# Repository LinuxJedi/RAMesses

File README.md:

# RAMesses

RAMesses is a plug and play Amiga 500/2000/CDTV board which will convert a 2MB 8375 Agnus to work in a 512KB/1MB motherboard and add 2MB of RAM.
RAMesses has two switchable modes, the first gives the full 2MB to Chip RAM, the second gives 1MB of Chip RAM and 512KB of Pseudo-Fast RAM.
This is for compatibility with older games.

The project is in two parts, one is a board that sits in the Agnus socket and the other is a board that sits in the Gary socket, the two boards need to be linked together with a four wire cable, preferably around 20cm in length.

# BOM

## Agnus

| Designator | Component |
| ---------- | --------- |
| C1 - C9    | 100nF 0603 capacitor |
| C10        | 22nF 0603 capacitor  |
| R1         | 150R 0603 resistor   |
| R2         | 4.7K 0603 resistor   |
| U4, U5, U7 | 74LVC2G157 VSSOP     |
| U1         | Winslow W9328 PLCC Plug |
| U2         | PLCC-84 socket |
| U3         | 74AHC1G08 SOT-23 |
| U6         | GM71C18163C SOJ-42 |
| JP1, J6    | 01x02 2.54mm horizontal pin header |

Notes:
1. The W9328 has been tested with the ZC158 variant, but all other height variants should would.
2. For U6 you could also use K4F151611, K4E151611 and AS4C1M16E5. Potentially other RAM chips will work too.

## Gary

This simply requires a 48pin DIP socket and 2 strips of 24pin machined pins.

# Assembly

Hand soldering the PLCC plug is highly recommended, this seems to create a stronger bond and this will be the most physically stressed part.

The two boards should be linked using four wires of roughly 26-32AWG. The order of the four wires is the opposite on each board (1 - 4 on one board, 4 - 1 on the other).

# Usage

You need an 2MB 8375 Agnus in the PLCC socket. Known models to work are:

* 318069-18 PAL
* 318069-10 PAL
* 390544-01 PAL
* 318069-11 NTSC
* 390544-02 NTSC

Please note that there are 1MB versions of the 8375 that are not compatible. The 2MB A3000 Agnus chips are not compatible.

Put a jumper on the bottom VBB jumper pins if the Agnus chip is marked as VBB.

The jumper on the top RAM Mode will give 2MB of chip RAM, the jumper removed will provide 1MB of chip RAM and 0.5MB of Pseudo-Fast RAM.

# Sponsorship

If you like this design and use it, please consider donating so I can design more Amiga things:

* Ko-fi: https://ko-fi.com/linuxjedi
* PayPal: https://paypal.me/linuxjedi

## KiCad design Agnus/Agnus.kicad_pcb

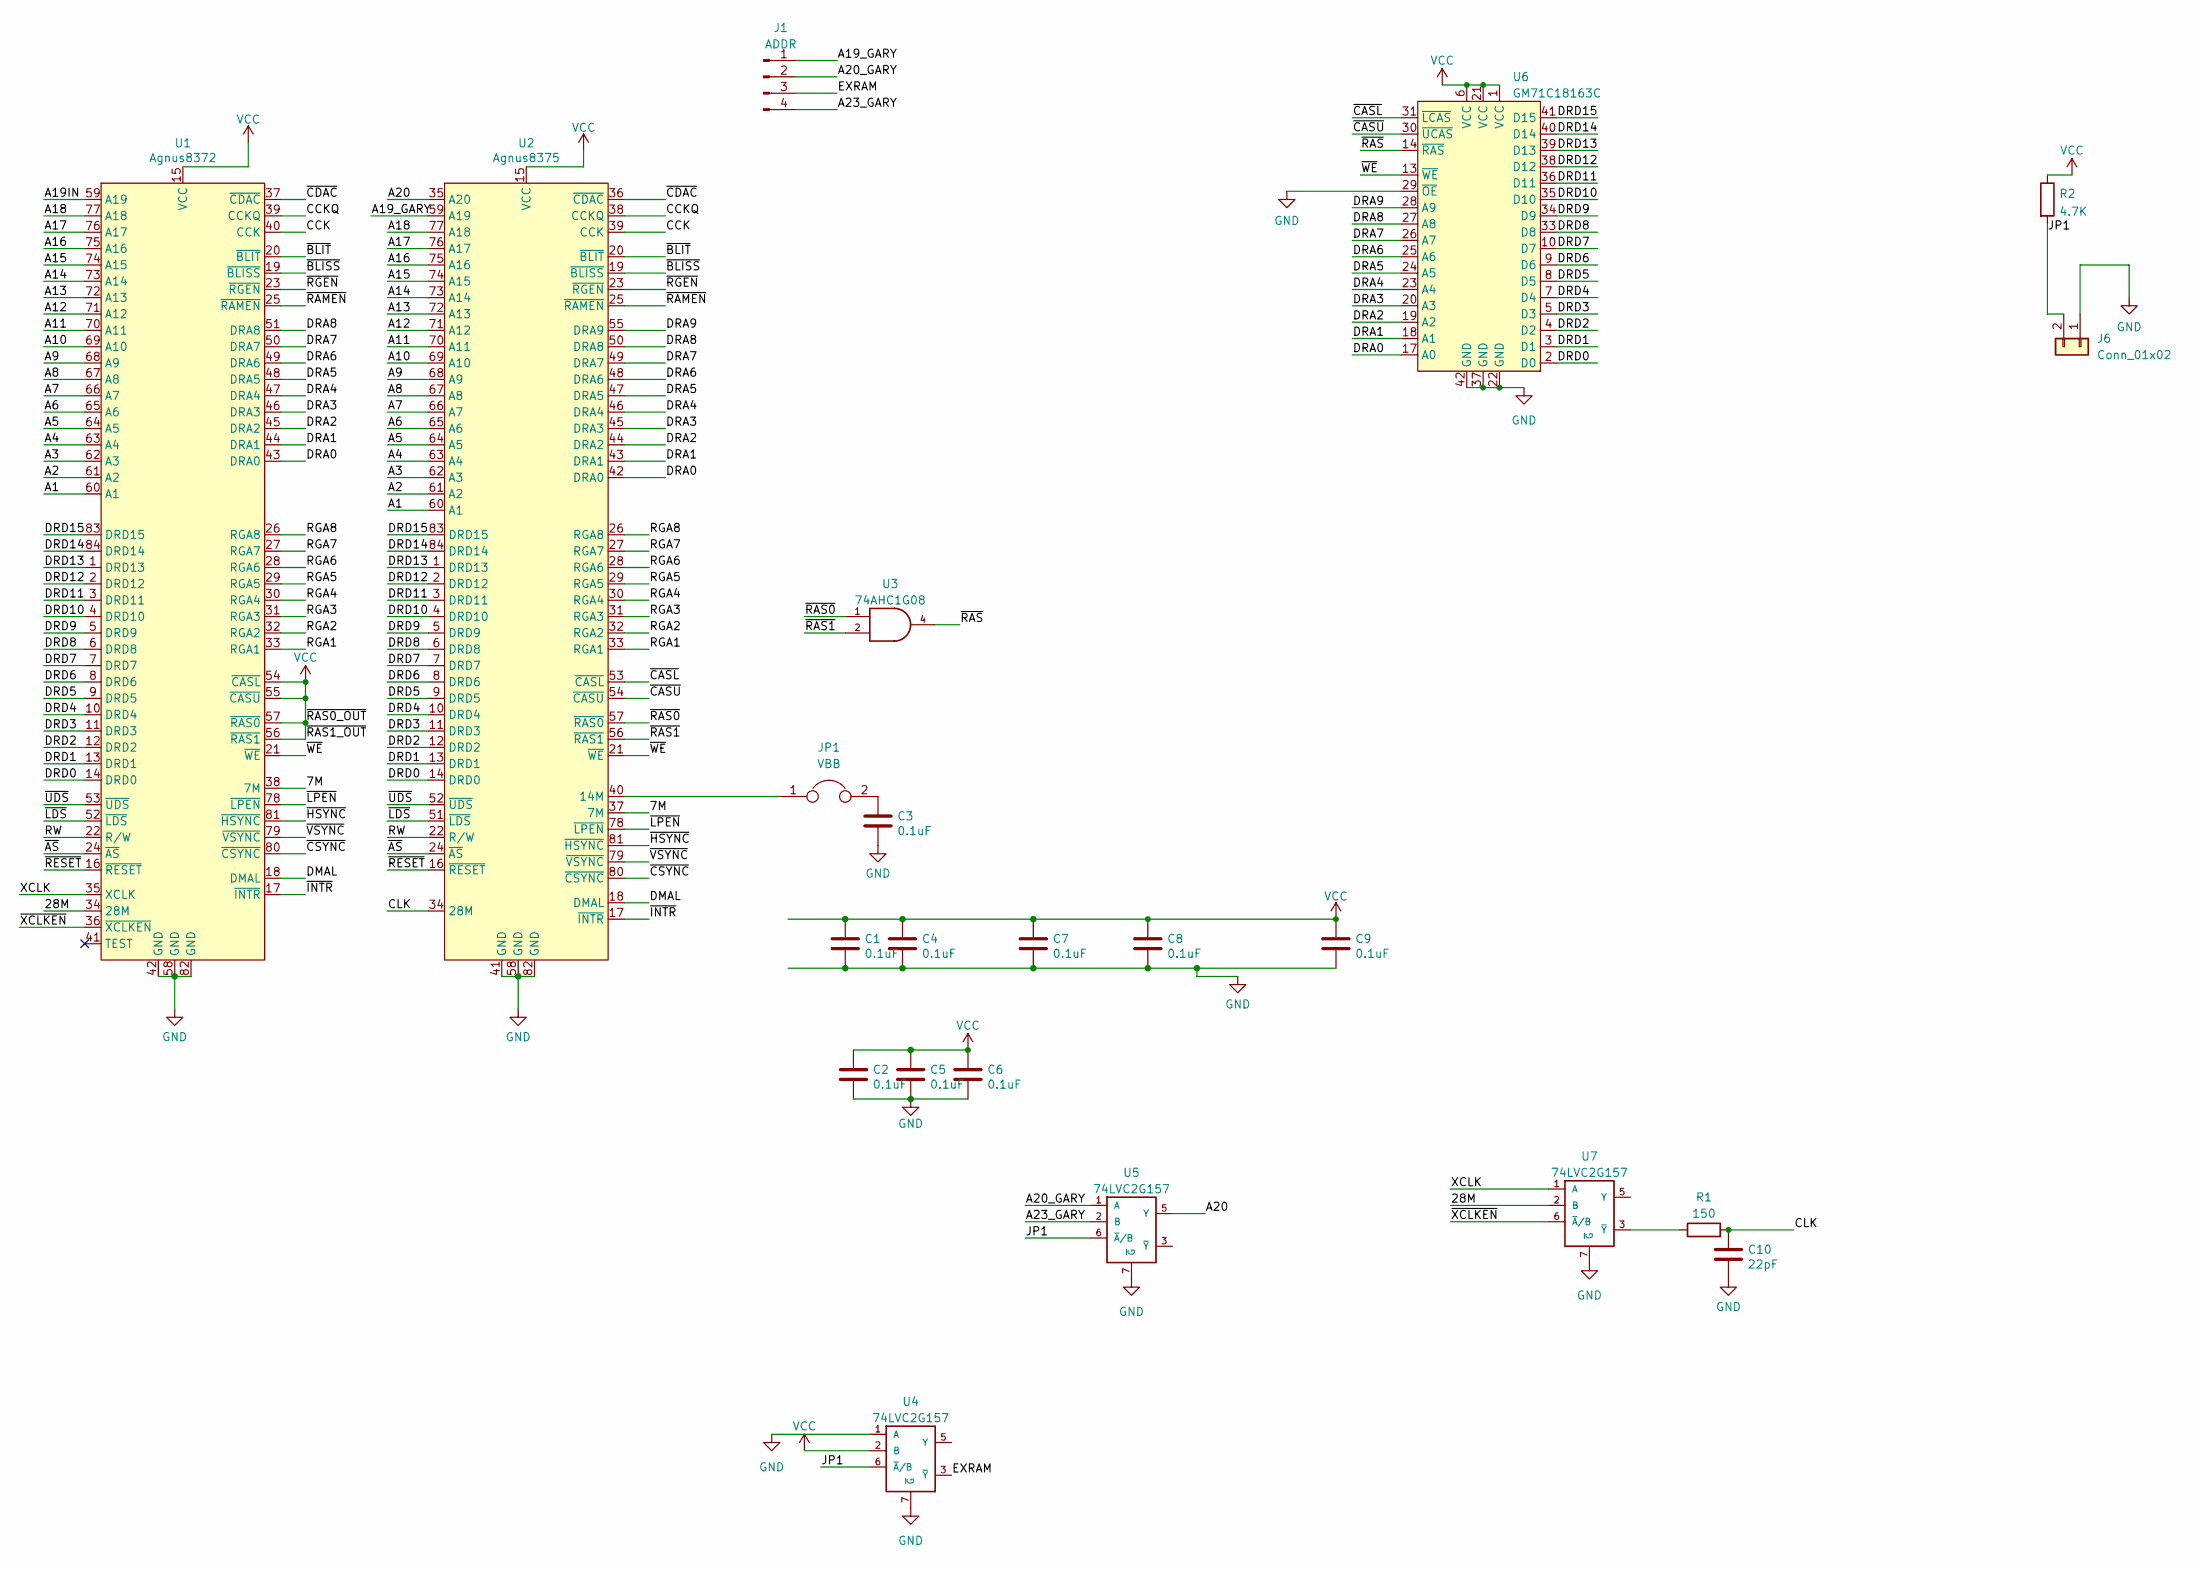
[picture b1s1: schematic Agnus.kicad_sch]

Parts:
C1, C2, C3, C4, C5, C6, C7, C8, C9: 0.1uF; C_0603_1608Metric_Pad1.08x0.95mm_HandSolder
C10: 22pF; C_0603_1608Metric_Pad1.08x0.95mm_HandSolder
J1: ADDR; PinSocket_1x04_P1.27mm_Vertical
J6: Conn_01x02; PinHeader_1x02_P2.54mm_Horizontal
JP1: VBB; PinHeader_1x02_P2.54mm_Horizontal
R1: 150; R_0603_1608Metric_Pad0.98x0.95mm_HandSolder
R2: 4.7K; R_0603_1608Metric_Pad0.98x0.95mm_HandSolder
U1: Agnus8372; PLCC Plug
U2: Agnus8375; PLCC-84_THT-Socket
U3: 74AHC1G08; SOT-23-5_HandSoldering
U4, U5, U7: 74LVC2G157; VSSOP-8_2.3x2mm_P0.5mm
U6: GM71C18163C; SOJ-42

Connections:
/7M: U1.38 (7M), U2.37 (7M)
/28M: U1.34 (28M), U7.2 (B)
/A1: U1.60 (A1), U2.60 (A1)
/A2: U1.61 (A2), U2.61 (A2)
/A3: U1.62 (A3), U2.62 (A3)
/A4: U1.63 (A4), U2.63 (A4)
/A5: U1.64 (A5), U2.64 (A5)
/A6: U1.65 (A6), U2.65 (A6)
/A7: U1.66 (A7), U2.66 (A7)
/A8: U1.67 (A8), U2.67 (A8)
/A9: U1.68 (A9), U2.68 (A9)
/A10: U1.69 (A10), U2.69 (A10)
/A11: U1.70 (A11), U2.70 (A11)
/A12: U1.71 (A12), U2.71 (A12)
/A13: U1.72 (A13), U2.72 (A13)
/A14: U1.73 (A14), U2.73 (A14)
/A15: U1.74 (A15), U2.74 (A15)
/A16: U1.75 (A16), U2.75 (A16)
/A17: U1.76 (A17), U2.76 (A17)
/A18: U1.77 (A18), U2.77 (A18)
/A19IN: U1.59 (A19)
/A19_GARY: J1.1, U2.59 (A19)
/A20: U2.35 (A20), U5.5 (Y)
/A20_GARY: J1.2, U5.1 (A)
/A23_GARY: J1.4, U5.2 (B)
/CCK: U1.40 (CCK), U2.39 (CCK)
/CCKQ: U1.39 (CCKQ), U2.38 (CCKQ)
/CLK: C10.1, R1.2, U2.34 (28M)
/DMAL: U1.18 (DMAL), U2.18 (DMAL)
/DRA0: U1.43 (DRA0), U2.42 (DRA0), U6.17 (A0)
/DRA1: U1.44 (DRA1), U2.43 (DRA1), U6.18 (A1)
/DRA2: U1.45 (DRA2), U2.44 (DRA2), U6.19 (A2)
/DRA3: U1.46 (DRA3), U2.45 (DRA3), U6.20 (A3)
/DRA4: U1.47 (DRA4), U2.46 (DRA4), U6.23 (A4)
/DRA5: U1.48 (DRA5), U2.47 (DRA5), U6.24 (A5)
/DRA6: U1.49 (DRA6), U2.48 (DRA6), U6.25 (A6)
/DRA7: U1.50 (DRA7), U2.49 (DRA7), U6.26 (A7)
/DRA8: U1.51 (DRA8), U2.50 (DRA8), U6.27 (A8)
/DRA9: U2.55 (DRA9), U6.28 (A9)
/DRD0: U1.14 (DRD0), U2.14 (DRD0), U6.2 (D0)
/DRD1: U1.13 (DRD1), U2.13 (DRD1), U6.3 (D1)
/DRD2: U1.12 (DRD2), U2.12 (DRD2), U6.4 (D2)
/DRD3: U1.11 (DRD3), U2.11 (DRD3), U6.5 (D3)
/DRD4: U1.10 (DRD4), U2.10 (DRD4), U6.7 (D4)
/DRD5: U1.9 (DRD5), U2.9 (DRD5), U6.8 (D5)
/DRD6: U1.8 (DRD6), U2.8 (DRD6), U6.9 (D6)
/DRD7: U1.7 (DRD7), U2.7 (DRD7), U6.10 (D7)
/DRD8: U1.6 (DRD8), U2.6 (DRD8), U6.33 (D8)
/DRD9: U1.5 (DRD9), U2.5 (DRD9), U6.34 (D9)
/DRD10: U1.4 (DRD10), U2.4 (DRD10), U6.35 (D10)
/DRD11: U1.3 (DRD11), U2.3 (DRD11), U6.36 (D11)
/DRD12: U1.2 (DRD12), U2.2 (DRD12), U6.38 (D12)
/DRD13: U1.1 (DRD13), U2.1 (DRD13), U6.39 (D13)
/DRD14: U1.84 (DRD14), U2.84 (DRD14), U6.40 (D14)
/DRD15: U1.83 (DRD15), U2.83 (DRD15), U6.41 (D15)
/EXRAM: J1.3, U4.3 (~Y)
/JP1: J6.2, R2.2, U4.6 (~A/B), U5.6 (~A/B)
/RGA1: U1.33 (RGA1), U2.33 (RGA1)
/RGA2: U1.32 (RGA2), U2.32 (RGA2)
/RGA3: U1.31 (RGA3), U2.31 (RGA3)
/RGA4: U1.30 (RGA4), U2.30 (RGA4)
/RGA5: U1.29 (RGA5), U2.29 (RGA5)
/RGA6: U1.28 (RGA6), U2.28 (RGA6)
/RGA7: U1.27 (RGA7), U2.27 (RGA7)
/RGA8: U1.26 (RGA8), U2.26 (RGA8)
/RW: U1.22 (R/W), U2.22 (R/W)
/XCLK: U1.35 (XCLK), U7.1 (A)
/~AS: U1.24 (~AS), U2.24 (~AS)
/~BLISS: U1.19 (~BLISS), U2.19 (~BLISS)
/~BLIT: U1.20 (~BLIT), U2.20 (~BLIT)
/~CASL: U2.53 (~CASL), U6.31 (~LCAS)
/~CASU: U2.54 (~CASU), U6.30 (~UCAS)
/~CDAC: U1.37 (~CDAC), U2.36 (~CDAC)
/~CSYNC: U1.80 (~CSYNC), U2.80 (~CSYNC)
/~HSYNC: U1.81 (~HSYNC), U2.81 (~HSYNC)
/~INTR: U1.17 (~INTR), U2.17 (~INTR)
/~LDS: U1.52 (~LDS), U2.51 (~LDS)
/~LPEN: U1.78 (~LPEN), U2.78 (~LPEN)
/~RAMEN: U1.25 (~RAMEN), U2.25 (~RAMEN)
/~RAS0: U2.57 (~RAS0), U3.1
/~RAS1: U2.56 (~RAS1), U3.2
/~RAS: U3.4, U6.14 (~RAS)
/~RESET: U1.16 (~RESET), U2.16 (~RESET)
/~RGEN: U1.23 (~RGEN), U2.23 (~RGEN)
/~UDS: U1.53 (~UDS), U2.52 (~UDS)
/~VSYNC: U1.79 (~VSYNC), U2.79 (~VSYNC)
/~WE: U1.21 (~WE), U2.21 (~WE), U6.13 (~WE)
/~XCLKEN: U1.36 (~XCLKEN), U7.6 (~A/B)
GND: C1.2, C2.2, C3.2, C4.2, C5.2, C6.2, C7.2, C8.2, C9.2, C10.2, J6.1, U1.42 (GND), U1.58 (GND), U1.82 (GND), U2.41 (GND), U2.58 (GND), U2.82 (GND), U3.3 (GND), U4.1 (A), U4.4 (GND), U4.7 (~G), U5.4 (GND), U5.7 (~G), U6.22 (GND), U6.29 (~OE), U6.37 (GND), U6.42 (GND), U7.4 (GND), U7.7 (~G)
unnamed: C3.1, JP1.2
unnamed: JP1.1, U2.40 (14M)
unnamed: R1.1, U7.3 (~Y)
VCC: C1.1, C2.1, C4.1, C5.1, C6.1, C7.1, C8.1, C9.1, R2.1, U1.15 (VCC), U1.54 (~CASL), U1.55 (~CASU), U1.56 (~RAS1), U1.57 (~RAS0), U2.15 (VCC), U3.5 (VCC), U4.2 (B), U4.8 (VCC), U5.8 (VCC), U6.1 (VCC), U6.6 (VCC), U6.21 (VCC), U7.8 (VCC)

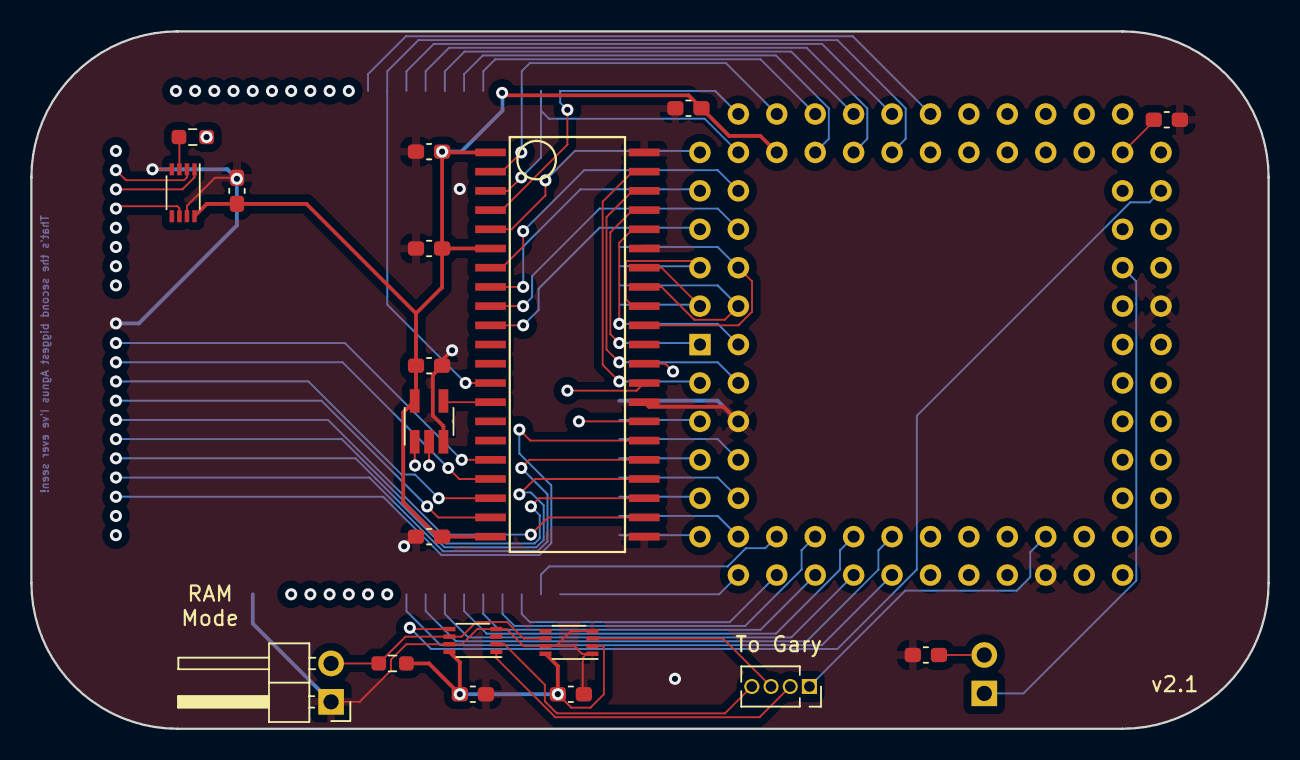
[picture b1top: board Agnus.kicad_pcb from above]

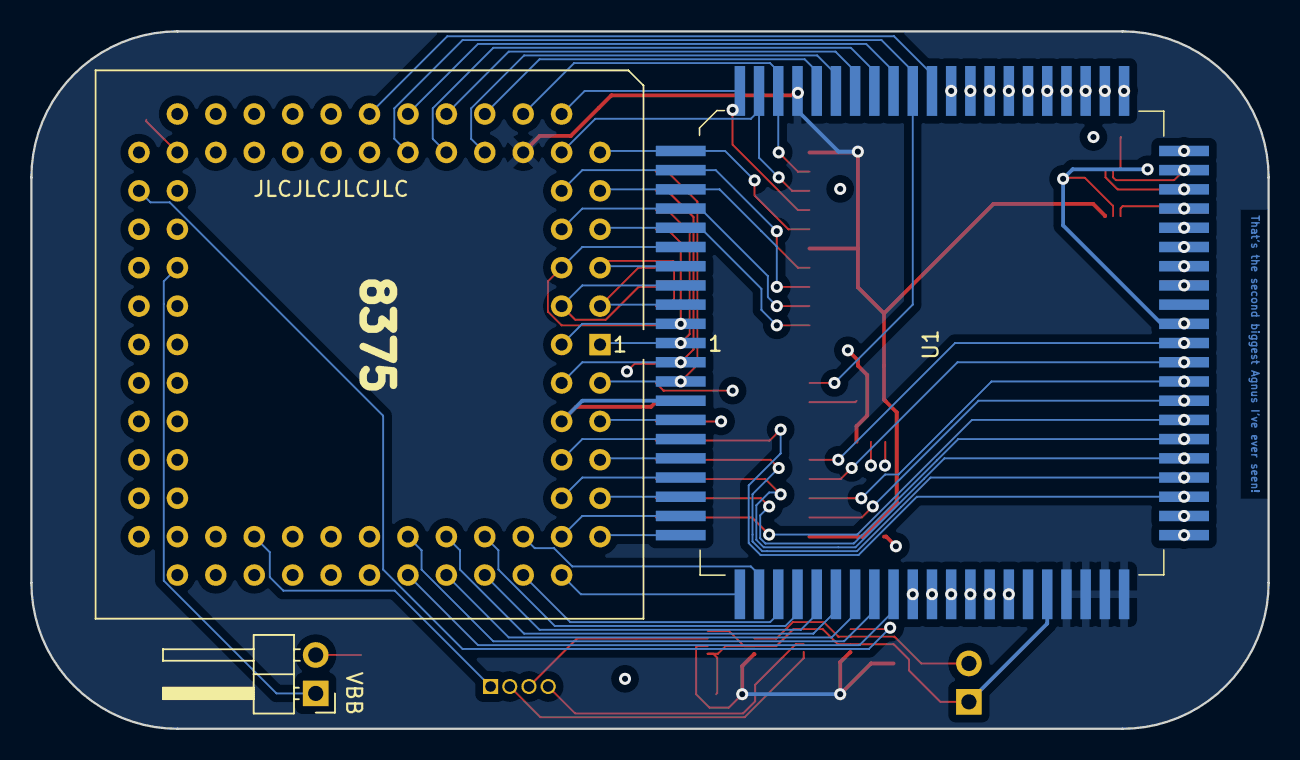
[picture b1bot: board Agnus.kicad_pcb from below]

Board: 4 copper layers, 81.8 x 46.1 mm, 22 parts (3 on the bottom side), 92 nets.

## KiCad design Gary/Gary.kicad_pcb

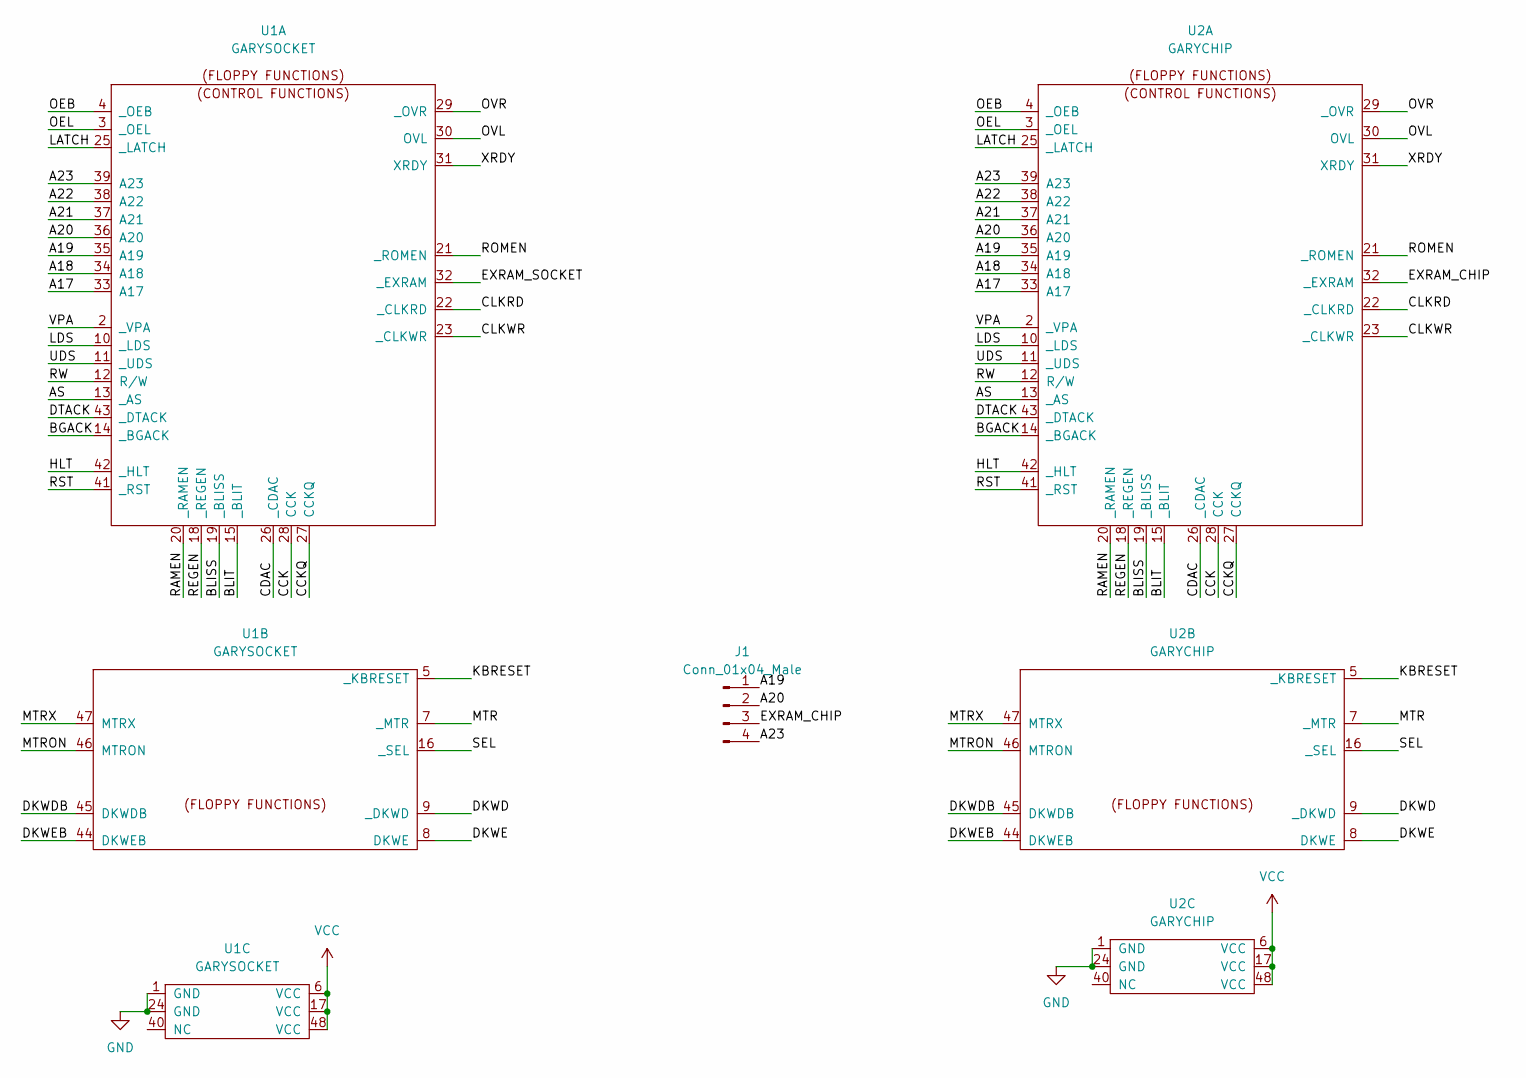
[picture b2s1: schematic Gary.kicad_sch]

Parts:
J1: Conn_01x04_Male; PinSocket_1x04_P1.27mm_Vertical
U1: GARYSOCKET; DIP-48_W15.24mm_Socket_LongPads
U2: GARYCHIP; DIP-48_W15.24mm_LongPads

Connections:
/A17: U1.33 (A17), U2.33 (A17)
/A18: U1.34 (A18), U2.34 (A18)
/A19: J1.1, U1.35 (A19), U2.35 (A19)
/A20: J1.2, U1.36 (A20), U2.36 (A20)
/A21: U1.37 (A21), U2.37 (A21)
/A22: U1.38 (A22), U2.38 (A22)
/A23: J1.4, U1.39 (A23), U2.39 (A23)
/AS: U1.13 (_AS), U2.13 (_AS)
/BGACK: U1.14 (_BGACK), U2.14 (_BGACK)
/BLISS: U1.19 (_BLISS), U2.19 (_BLISS)
/BLIT: U1.15 (_BLIT), U2.15 (_BLIT)
/CCK: U1.28 (CCK), U2.28 (CCK)
/CCKQ: U1.27 (CCKQ), U2.27 (CCKQ)
/CDAC: U1.26 (_CDAC), U2.26 (_CDAC)
/CLKRD: U1.22 (_CLKRD), U2.22 (_CLKRD)
/CLKWR: U1.23 (_CLKWR), U2.23 (_CLKWR)
/DKWD: U1.9 (_DKWD), U2.9 (_DKWD)
/DKWDB: U1.45 (DKWDB), U2.45 (DKWDB)
/DKWE: U1.8 (DKWE), U2.8 (DKWE)
/DKWEB: U1.44 (DKWEB), U2.44 (DKWEB)
/DTACK: U1.43 (_DTACK), U2.43 (_DTACK)
/EXRAM_CHIP: J1.3, U2.32 (_EXRAM)
/EXRAM_SOCKET: U1.32 (_EXRAM)
/HLT: U1.42 (_HLT), U2.42 (_HLT)
/KBRESET: U1.5 (_KBRESET), U2.5 (_KBRESET)
/LATCH: U1.25 (_LATCH), U2.25 (_LATCH)
/LDS: U1.10 (_LDS), U2.10 (_LDS)
/MTR: U1.7 (_MTR), U2.7 (_MTR)
/MTRON: U1.46 (MTRON), U2.46 (MTRON)
/MTRX: U1.47 (MTRX), U2.47 (MTRX)
/OEB: U1.4 (_OEB), U2.4 (_OEB)
/OEL: U1.3 (_OEL), U2.3 (_OEL)
/OVL: U1.30 (OVL), U2.30 (OVL)
/OVR: U1.29 (_OVR), U2.29 (_OVR)
/RAMEN: U1.20 (_RAMEN), U2.20 (_RAMEN)
/REGEN: U1.18 (_REGEN), U2.18 (_REGEN)
/ROMEN: U1.21 (_ROMEN), U2.21 (_ROMEN)
/RST: U1.41 (_RST), U2.41 (_RST)
/RW: U1.12 (R/W), U2.12 (R/W)
/SEL: U1.16 (_SEL), U2.16 (_SEL)
/UDS: U1.11 (_UDS), U2.11 (_UDS)
/VPA: U1.2 (_VPA), U2.2 (_VPA)
/XRDY: U1.31 (XRDY), U2.31 (XRDY)
GND: U1.1 (GND), U1.24 (GND), U2.1 (GND), U2.24 (GND)
VCC: U1.6 (VCC), U1.17 (VCC), U1.48 (VCC), U2.6 (VCC), U2.17 (VCC), U2.48 (VCC)

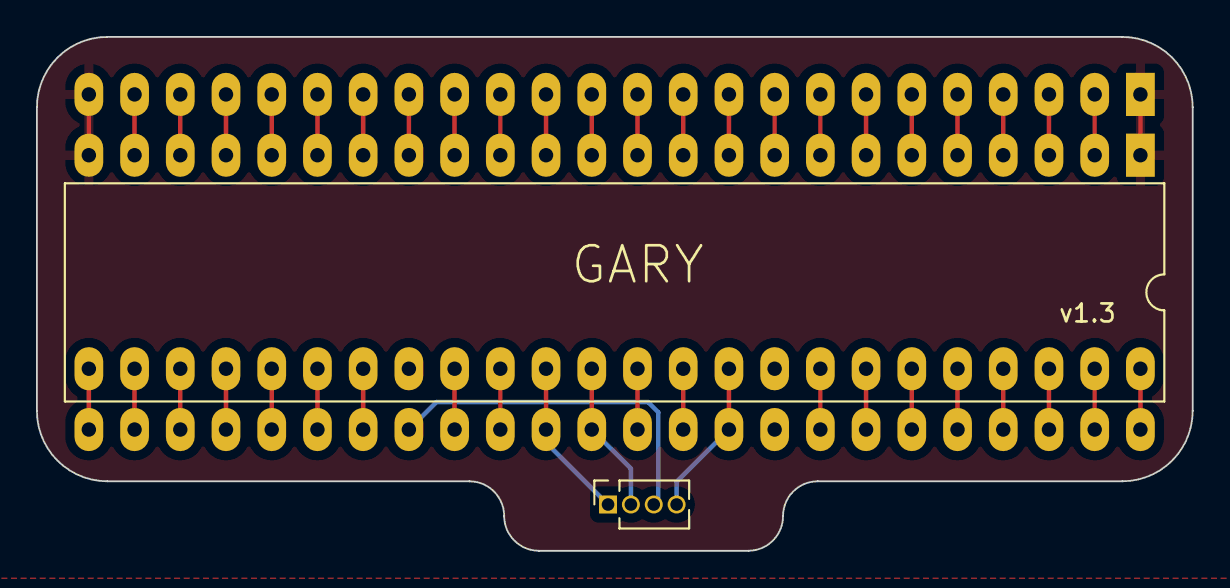
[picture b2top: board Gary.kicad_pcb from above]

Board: 2 copper layers, 64.2 x 28.5 mm, 3 parts (0 on the bottom side), 44 nets.

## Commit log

2023-02-19 Initial push
2023-02-19 Add gerbers
